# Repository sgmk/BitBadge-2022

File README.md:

### BitBadge

BitBadge is a creative reflow soldering badge. Designed by http://www.gaudi.ch

### Instructions

Place topleds on the grid to make your very own design.

Draft different designs with the empty canvas. Start with single colour and go beyond later. 

Download a .pdf HandOut for drafting:
https://github.com/sgmk/BitBadge-2022/blob/master/HandOuts/BitBadge_drafting.pdf

Or use the amazing online tool made by Bernhard: https://bernhardwagner.net/sgmk/bitbadge.html

The LEDs have a direction! Look for the little corner the is angled.
Make sure all the LEDs point towards the same direction.

Download and print the .pdf HandOut: 
https://github.com/sgmk/BitBadge-2022/blob/master/HandOuts/BitBadge_handout.pdf

The super switch can invert polarity. So both direction will be good. And for super advanced effects you can put 2 different colours in different direction and switch to choose which ones are lit. Or use external powers and switching for blinkeshit!

### License

BitBadge, all design files and software are licensed under a GNU GENERAL PUBLIC LICENSE. See license file in the repository.

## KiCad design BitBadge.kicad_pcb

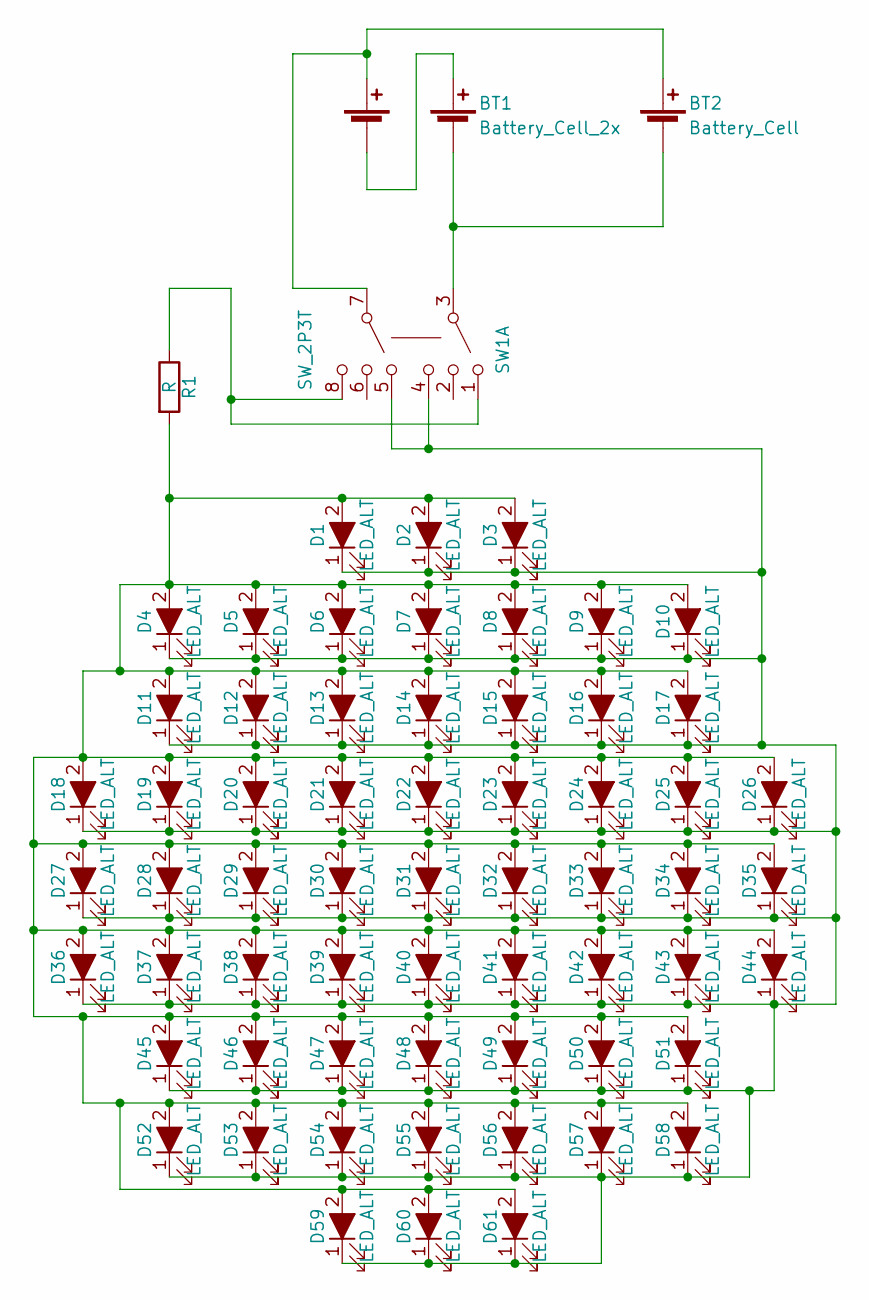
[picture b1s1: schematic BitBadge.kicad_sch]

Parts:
BT1: Battery_Cell_2x; BAT_HOLDER_AAA_DOUBLE_BITBADGE
BT2: Battery_Cell; CR2032_Holder
D1, D2, D3, D4, D5, D6, D7, D8, D9, D10, D11, D12, D13, D14, D15, D16, D17, D18, D19, D20, D21, D22, D23, D24, D25, D26, D27, D28, D29, D30, D31, D32, D33, D34, D35, D36, D37, D38, D39, D40, D41, D42, D43, D44, D45, D46, D47, D48, D49, D50, D51, D52, D53, D54, D55, D56, D57, D58, D59, D60, D61: LED_ALT; TopLed_BitBadge
R1: R; R_1210_HandSoldering
SW1: SW_2P3T; SWITCH_MSS23D19

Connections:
unnamed: BT1.2 (-), BT1.3 (+)
unnamed: BT1.1 (+), BT2.1 (+), SW1.7
unnamed: BT1.4 (-), BT2.2 (-), SW1.3
unnamed: D1.2 (A), D2.2 (A), D3.2 (A), D4.2 (A), D5.2 (A), D6.2 (A), D7.2 (A), D8.2 (A), D9.2 (A), D10.2 (A), D11.2 (A), D12.2 (A), D13.2 (A), D14.2 (A), D15.2 (A), D16.2 (A), D17.2 (A), D18.2 (A), D19.2 (A), D20.2 (A), D21.2 (A), D22.2 (A), D23.2 (A), D24.2 (A), D25.2 (A), D26.2 (A), D27.2 (A), D28.2 (A), D29.2 (A), D30.2 (A), D31.2 (A), D32.2 (A), D33.2 (A), D34.2 (A), D35.2 (A), D36.2 (A), D37.2 (A), D38.2 (A), D39.2 (A), D40.2 (A), D41.2 (A), D42.2 (A), D43.2 (A), D44.2 (A), D45.2 (A), D46.2 (A), D47.2 (A), D48.2 (A), D49.2 (A), D50.2 (A), D51.2 (A), D52.2 (A), D53.2 (A), D54.2 (A), D55.2 (A), D56.2 (A), D57.2 (A), D58.2 (A), D59.2 (A), D60.2 (A), D61.2 (A), R1.2
unnamed: D1.1 (K), D2.1 (K), D3.1 (K), D4.1 (K), D5.1 (K), D6.1 (K), D7.1 (K), D8.1 (K), D9.1 (K), D10.1 (K), D11.1 (K), D12.1 (K), D13.1 (K), D14.1 (K), D15.1 (K), D16.1 (K), D17.1 (K), D18.1 (K), D19.1 (K), D20.1 (K), D21.1 (K), D22.1 (K), D23.1 (K), D24.1 (K), D25.1 (K), D26.1 (K), D27.1 (K), D28.1 (K), D29.1 (K), D30.1 (K), D31.1 (K), D32.1 (K), D33.1 (K), D34.1 (K), D35.1 (K), D36.1 (K), D37.1 (K), D38.1 (K), D39.1 (K), D40.1 (K), D41.1 (K), D42.1 (K), D43.1 (K), D44.1 (K), D45.1 (K), D46.1 (K), D47.1 (K), D48.1 (K), D49.1 (K), D50.1 (K), D51.1 (K), D52.1 (K), D53.1 (K), D54.1 (K), D55.1 (K), D56.1 (K), D57.1 (K), D58.1 (K), D59.1 (K), D60.1 (K), D61.1 (K), SW1.4, SW1.5
unnamed: R1.1, SW1.1, SW1.8

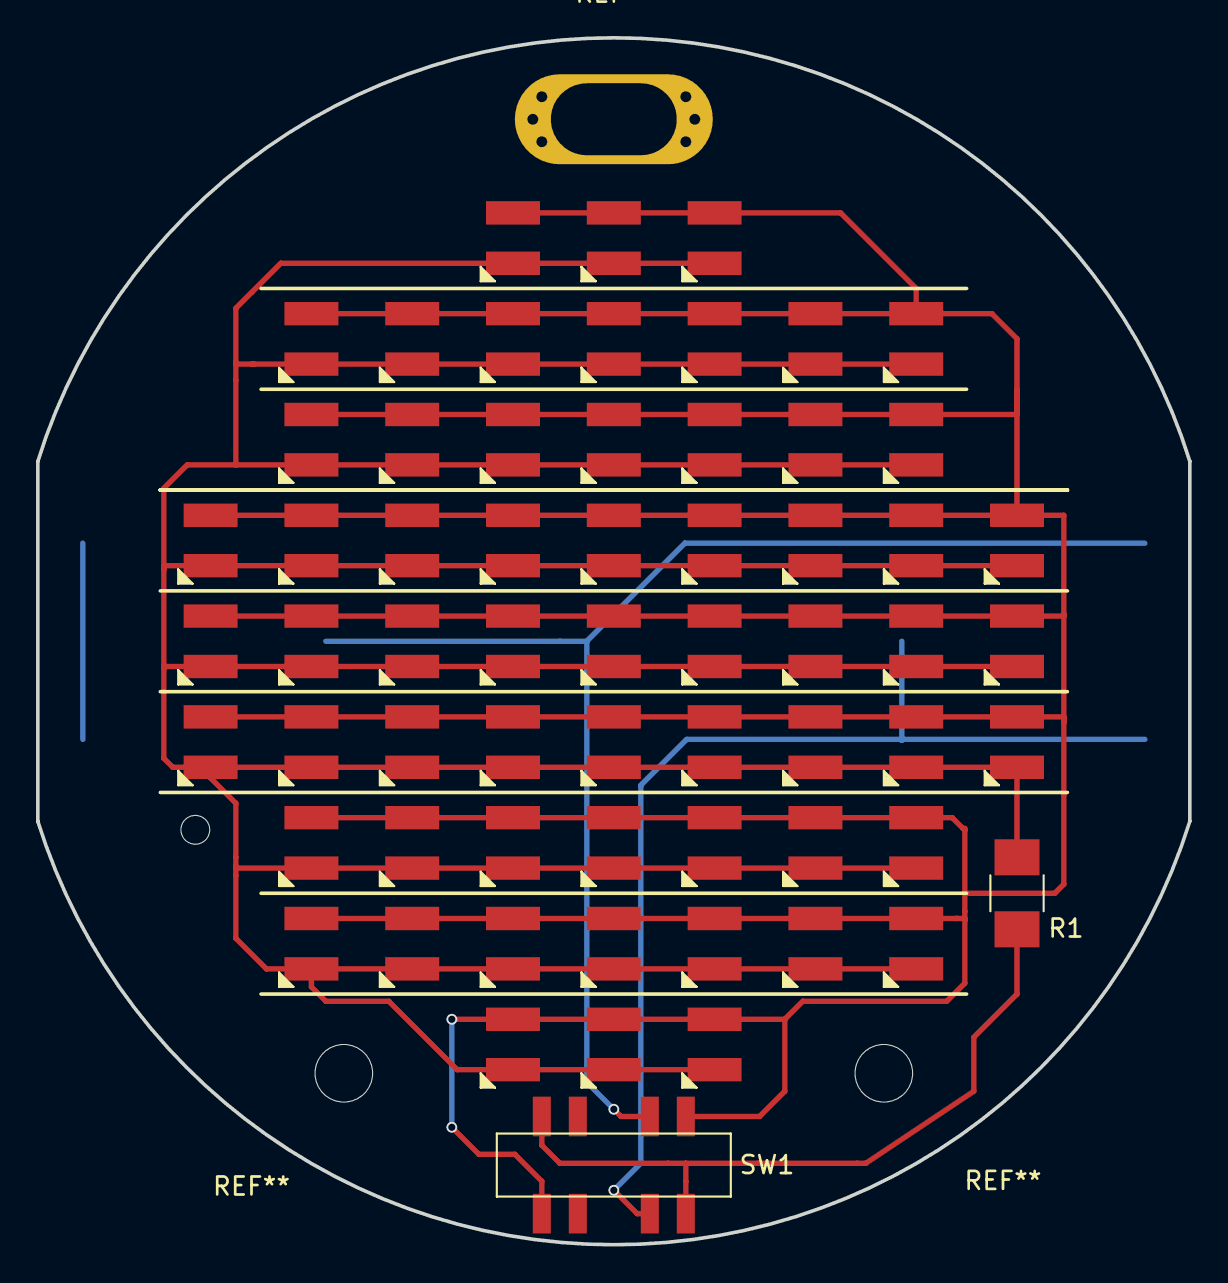
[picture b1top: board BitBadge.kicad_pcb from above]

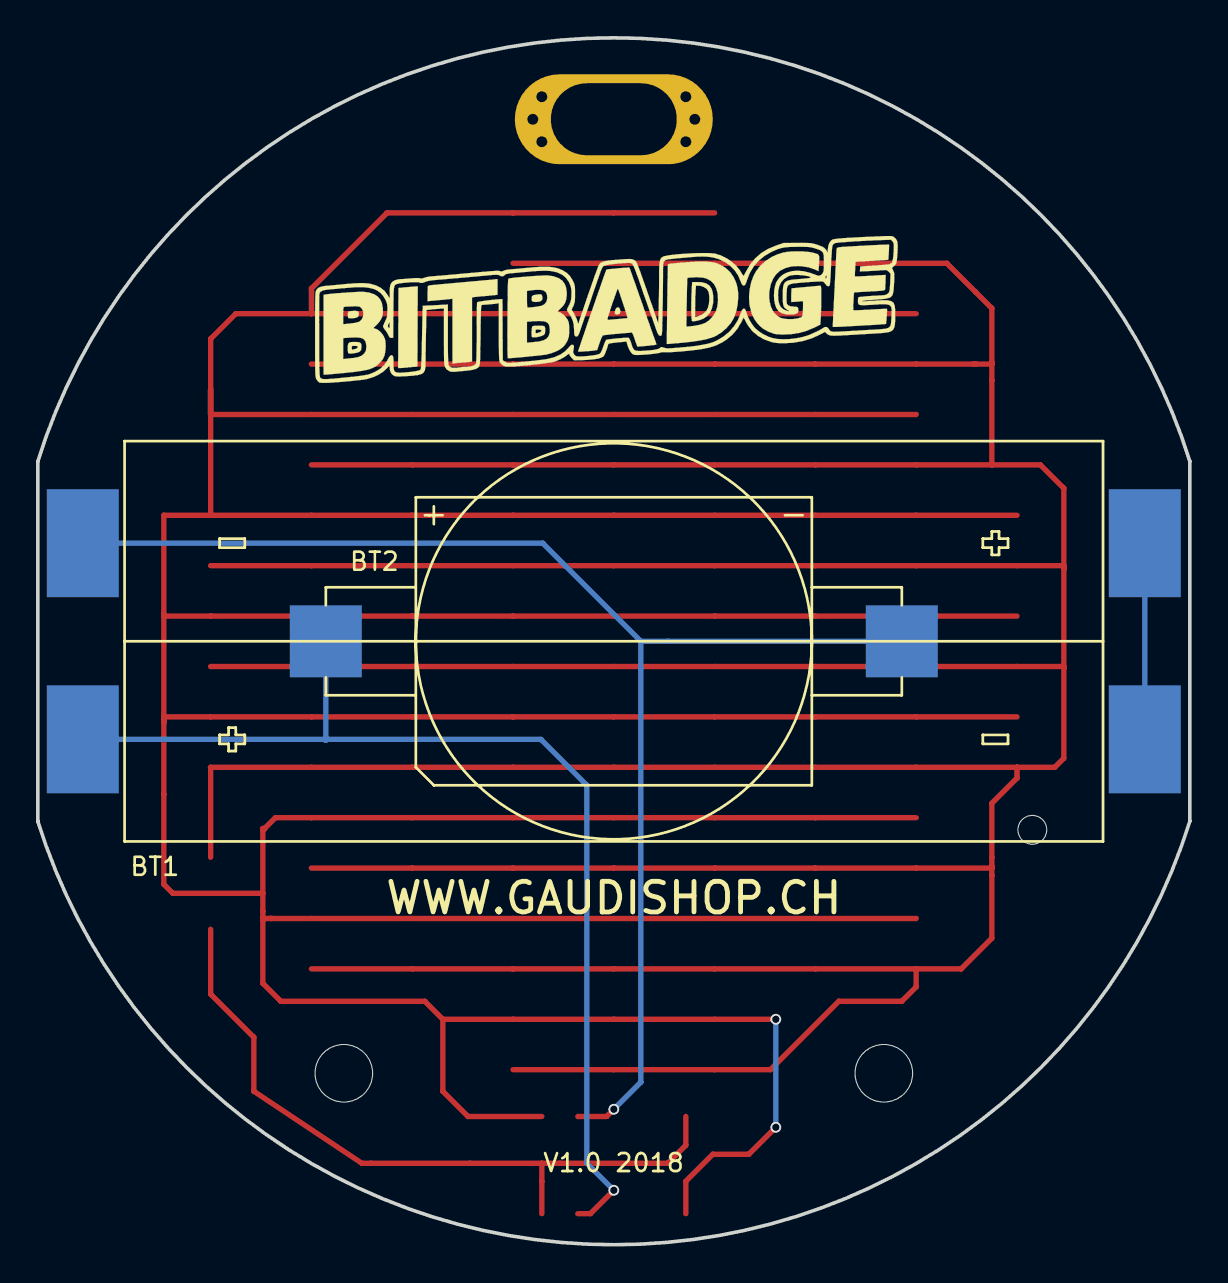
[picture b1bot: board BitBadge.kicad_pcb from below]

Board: 2 copper layers, 64.0 x 67.1 mm, 65 parts (2 on the bottom side), 6 nets.

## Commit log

2024-10-04 new handouts and kicad8
2024-10-04 editing readme
